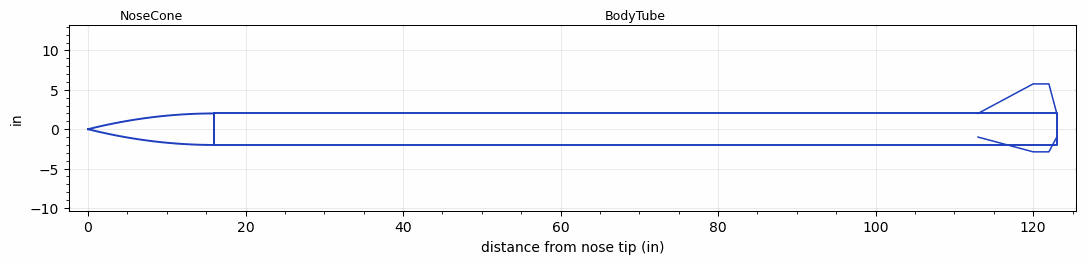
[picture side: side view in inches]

<RASAeroDocument>
 <FileVersion>2</FileVersion>
 <RocketDesign>
  <NoseCone>
   <Length>16</Length>
   <Diameter>4</Diameter>
   <Shape>Parabolic</Shape>
   <Location>0</Location>
  </NoseCone>
  <BodyTube>
   <Length>107</Length>
   <Diameter>4</Diameter>
   <Location>16</Location>
   <Fin>
    <Count>3</Count>
    <Chord>10</Chord>
    <Span>3.75</Span>
    <SweepDistance>7</SweepDistance>
    <TipChord>2</TipChord>
    <Thickness>0.25</Thickness>
    <LERadius>0.125</LERadius>
    <Location>10</Location>
    <AirfoilSection>Double Wedge</AirfoilSection>
    <FX1>1</FX1>
    <FX3>1</FX3>
   </Fin>
  </BodyTube>
  <Surface>Smooth Paint</Surface>
  <ModifiedBarrowman>False</ModifiedBarrowman>
  <Turbulence>False</Turbulence>
  <UseBooster1>False</UseBooster1>
  <UseBooster2>False</UseBooster2>
 </RocketDesign>
 <LaunchSite>
  <Altitude>5000</Altitude>
  <Pressure>0</Pressure>
  <RodAngle>7</RodAngle>
  <RodLength>4</RodLength>
  <Temperature>95</Temperature>
  <WindSpeed>8</WindSpeed>
 </LaunchSite>
 <Recovery>
  <Altitude1>1000</Altitude1>
  <Altitude2>1000</Altitude2>
  <DeviceType1>None</DeviceType1>
  <DeviceType2>None</DeviceType2>
  <Event1>False</Event1>
  <Event2>False</Event2>
  <Size1>1</Size1>
  <Size2>1</Size2>
  <EventType1>None</EventType1>
  <EventType2>None</EventType2>
  <CD1>1.33</CD1>
  <CD2>1.33</CD2>
 </Recovery>
 <SimulationList>
  <Simulation>
   <SustainerEngine>N2540-GR-P  (CTI)</SustainerEngine>
   <SustainerLaunchWt>66</SustainerLaunchWt>
   <SustainerNozzleDiameter>1.5</SustainerNozzleDiameter>
   <SustainerCG>81</SustainerCG>
   <SustainerIgnitionDelay>0</SustainerIgnitionDelay>
   <Booster1SeparationDelay>0</Booster1SeparationDelay>
   <Booster1IgnitionDelay>0</Booster1IgnitionDelay>
   <IncludeBooster1>False</IncludeBooster1>
   <Booster2Delay>0</Booster2Delay>
   <IncludeBooster2>False</IncludeBooster2>
   <TimetoApogee>48.93779</TimetoApogee>
   <MaxAltitude>39830.29</MaxAltitude>
   <MaxVelocity>2003.001</MaxVelocity>
   <OptimumWt>65.625</OptimumWt>
   <OptimumMaxAlt>65.625</OptimumMaxAlt>
  </Simulation>
  <Simulation>
   <SustainerEngine>N1975-GR  (CTI)</SustainerEngine>
   <SustainerLaunchWt>60</SustainerLaunchWt>
   <SustainerNozzleDiameter>1.5</SustainerNozzleDiameter>
   <SustainerCG>80</SustainerCG>
   <SustainerIgnitionDelay>0</SustainerIgnitionDelay>
   <Booster1SeparationDelay>0</Booster1SeparationDelay>
   <Booster1IgnitionDelay>0</Booster1IgnitionDelay>
   <IncludeBooster1>False</IncludeBooster1>
   <Booster2Delay>0</Booster2Delay>
   <IncludeBooster2>False</IncludeBooster2>
   <TimetoApogee>42.72884</TimetoApogee>
   <MaxAltitude>29175.56</MaxAltitude>
   <MaxVelocity>1679.016</MaxVelocity>
  </Simulation>
  <Simulation>
   <SustainerEngine>N2501-WH-P  (CTI)</SustainerEngine>
   <SustainerLaunchWt>60</SustainerLaunchWt>
   <SustainerNozzleDiameter>1</SustainerNozzleDiameter>
   <SustainerCG>80</SustainerCG>
   <SustainerIgnitionDelay>0</SustainerIgnitionDelay>
   <Booster1SeparationDelay>0</Booster1SeparationDelay>
   <Booster1IgnitionDelay>0</Booster1IgnitionDelay>
   <IncludeBooster1>False</IncludeBooster1>
   <Booster2Delay>0</Booster2Delay>
   <IncludeBooster2>False</IncludeBooster2>
   <TimetoApogee>43.89864</TimetoApogee>
   <MaxAltitude>32777.43</MaxAltitude>
   <MaxVelocity>1809.945</MaxVelocity>
  </Simulation>
  <Simulation>
   <SustainerEngine>N2600-SK  (CTI)</SustainerEngine>
   <SustainerLaunchWt>60</SustainerLaunchWt>
   <SustainerNozzleDiameter>1</SustainerNozzleDiameter>
   <SustainerCG>80</SustainerCG>
   <SustainerIgnitionDelay>0</SustainerIgnitionDelay>
   <Booster1SeparationDelay>0</Booster1SeparationDelay>
   <Booster1IgnitionDelay>0</Booster1IgnitionDelay>
   <IncludeBooster1>False</IncludeBooster1>
   <Booster2Delay>0</Booster2Delay>
   <IncludeBooster2>False</IncludeBooster2>
   <TimetoApogee>35.54004</TimetoApogee>
   <MaxAltitude>20372.97</MaxAltitude>
   <MaxVelocity>1333.404</MaxVelocity>
  </Simulation>
  <Simulation>
   <SustainerEngine>N2850-BS  (CTI)</SustainerEngine>
   <SustainerLaunchWt>61</SustainerLaunchWt>
   <SustainerNozzleDiameter>1</SustainerNozzleDiameter>
   <SustainerCG>80</SustainerCG>
   <SustainerIgnitionDelay>0</SustainerIgnitionDelay>
   <Booster1SeparationDelay>0</Booster1SeparationDelay>
   <Booster1IgnitionDelay>0</Booster1IgnitionDelay>
   <IncludeBooster1>False</IncludeBooster1>
   <Booster2Delay>0</Booster2Delay>
   <IncludeBooster2>False</IncludeBooster2>
   <TimetoApogee>40.36923</TimetoApogee>
   <MaxAltitude>27116.07</MaxAltitude>
   <MaxVelocity>1607.977</MaxVelocity>
  </Simulation>
  <Simulation>
   <SustainerEngine>N2900-CL  (CTI)</SustainerEngine>
   <SustainerLaunchWt>61</SustainerLaunchWt>
   <SustainerNozzleDiameter>1</SustainerNozzleDiameter>
   <SustainerCG>80</SustainerCG>
   <SustainerIgnitionDelay>0</SustainerIgnitionDelay>
   <Booster1SeparationDelay>0</Booster1SeparationDelay>
   <Booster1IgnitionDelay>0</Booster1IgnitionDelay>
   <IncludeBooster1>False</IncludeBooster1>
   <Booster2Delay>0</Booster2Delay>
   <IncludeBooster2>False</IncludeBooster2>
   <TimetoApogee>47.83798</TimetoApogee>
   <MaxAltitude>39840.84</MaxAltitude>
   <MaxVelocity>2063.873</MaxVelocity>
  </Simulation>
 </SimulationList>
</RASAeroDocument>
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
